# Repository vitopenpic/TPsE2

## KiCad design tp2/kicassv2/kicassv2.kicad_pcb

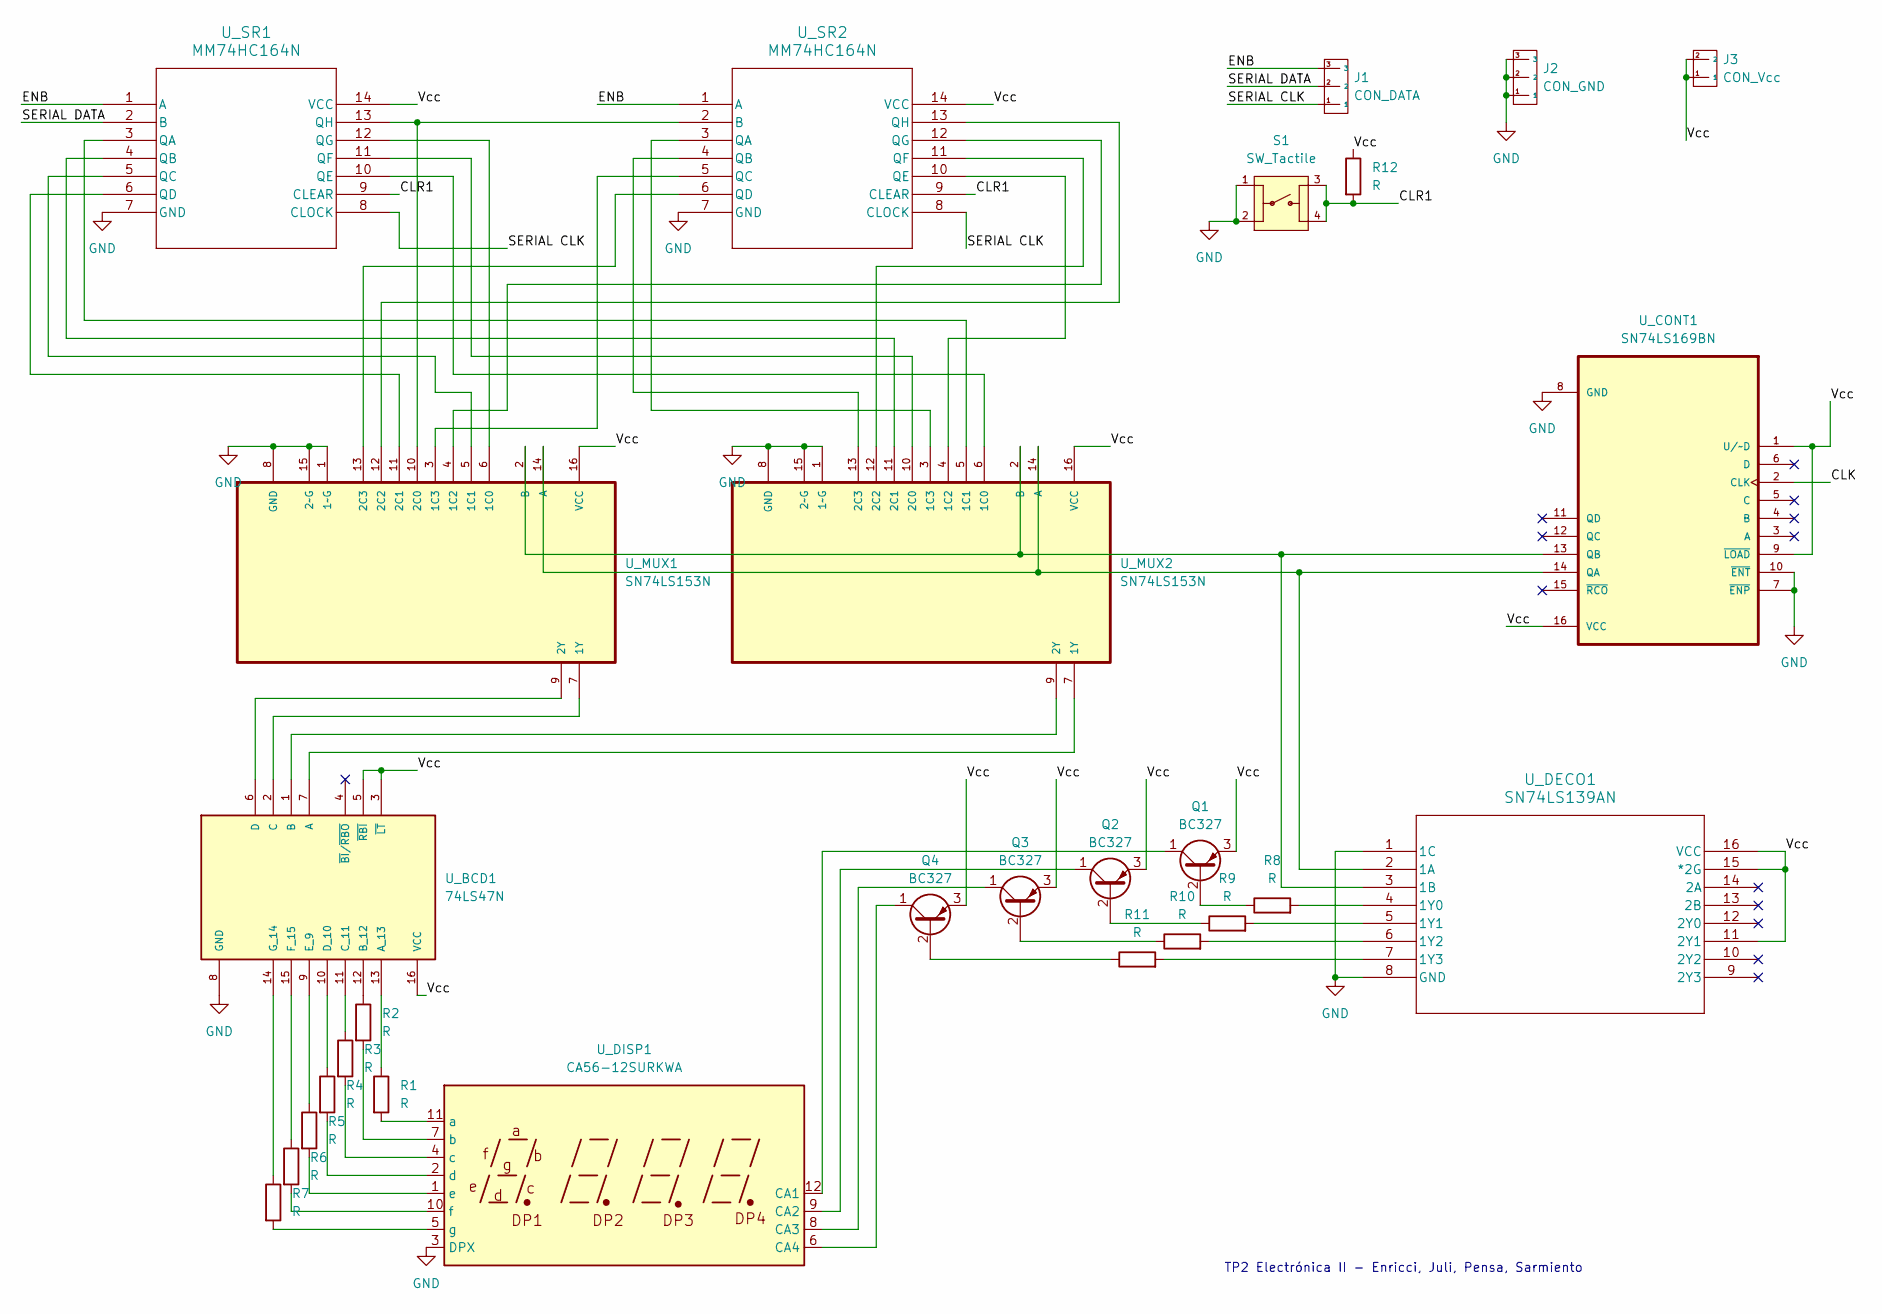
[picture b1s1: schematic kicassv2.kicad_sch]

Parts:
J1: CON_DATA; PinHeader_1x03_P2.54mm_Vertical
J2: CON_GND; PinHeader_1x03_P2.54mm_Vertical
J3: CON_Vcc; PinHeader_1x02_P2.54mm_Vertical
Q1, Q2, Q3, Q4: BC327; TO-92_Inline
R1, R2, R3, R4, R5, R6, R7, R8, R9, R10, R11, R12: R; R_0.25W
S1: SW_Tactile; PARTREV C10
U_BCD1: 74LS47N; PARTREV March 1988
U_CONT1: SN74LS169BN; 74LS169
U_DECO1: SN74LS139AN; 74LS139
U_DISP1: CA56-12SURKWA
U_MUX1, U_MUX2: SN74LS153N; 74LS153; MPN SN74LS153N
U_SR1, U_SR2: MM74HC164N; 74HC164

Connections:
/CLK: U_CONT1.2 (CLK)
/CLR1: R12.2, S1.3, S1.4, U_SR1.9 (CLEAR), U_SR2.9 (CLEAR)
/ENB: J1.3, U_SR1.1 (A), U_SR2.1 (A)
/SERIAL CLK: J1.1, U_SR1.8 (CLOCK), U_SR2.8 (CLOCK)
/SERIAL DATA: J1.2, U_SR1.2 (B)
/Vcc: J3.1, J3.2, Q1.3 (E), Q2.3 (E), Q3.3 (E), Q4.3 (E), R12.1, U_BCD1.3 (~LT), U_BCD1.4 (~BI/~RBO), U_BCD1.5 (~RBI), U_BCD1.16 (VCC), U_CONT1.1 (U/~D), U_CONT1.9 (~LOAD), U_CONT1.16 (VCC), U_DECO1.9 (2Y3), U_DECO1.10 (2Y2), U_DECO1.11 (2Y1), U_DECO1.12 (2Y0), U_DECO1.15 (*2G), U_DECO1.16 (VCC), U_MUX1.16 (VCC), U_MUX2.16 (VCC), U_SR1.14 (VCC), U_SR2.14 (VCC)
GND: J2.1, J2.2, J2.3, S1.1, S1.2, U_BCD1.8 (GND), U_CONT1.7 (~ENP), U_CONT1.8 (GND), U_CONT1.10 (~ENT), U_DECO1.1 (1C), U_DECO1.8 (GND), U_DISP1.3 (DPX), U_MUX1.1 (1~G), U_MUX1.8 (GND), U_MUX1.15 (2~G), U_MUX2.1 (1~G), U_MUX2.8 (GND), U_MUX2.15 (2~G), U_SR1.7 (GND), U_SR2.7 (GND)
unnamed: Q1.2 (B), R8.1
unnamed: Q1.1 (C), U_DISP1.12 (CA1)
unnamed: Q2.2 (B), R9.1
unnamed: Q2.1 (C), U_DISP1.9 (CA2)
unnamed: Q3.2 (B), R10.1
unnamed: Q3.1 (C), U_DISP1.8 (CA3)
unnamed: Q4.2 (B), R11.1
unnamed: Q4.1 (C), U_DISP1.6 (CA4)
unnamed: U_BCD1.7 (A), U_MUX2.7 (1Y)
unnamed: R1.1, U_BCD1.13 (A_13)
unnamed: U_BCD1.1 (B), U_MUX2.9 (2Y)
unnamed: R2.1, U_BCD1.12 (B_12)
unnamed: U_BCD1.2 (C), U_MUX1.7 (1Y)
unnamed: R3.1, U_BCD1.11 (C_11)
unnamed: U_BCD1.6 (D), U_MUX1.9 (2Y)
unnamed: R4.1, U_BCD1.10 (D_10)
unnamed: R5.1, U_BCD1.9 (E_9)
unnamed: R6.1, U_BCD1.15 (F_15)
unnamed: R7.1, U_BCD1.14 (G_14)
unnamed: U_CONT1.14 (QA), U_DECO1.2 (1A), U_MUX1.14 (A), U_MUX2.14 (A)
unnamed: U_CONT1.13 (QB), U_DECO1.3 (1B), U_MUX1.2 (B), U_MUX2.2 (B)
unnamed: R8.2, U_DECO1.4 (1Y0)
unnamed: R9.2, U_DECO1.5 (1Y1)
unnamed: R10.2, U_DECO1.6 (1Y2)
unnamed: R11.2, U_DECO1.7 (1Y3)
unnamed: R1.2, U_DISP1.11 (a)
unnamed: R2.2, U_DISP1.7 (b)
unnamed: R3.2, U_DISP1.4 (c)
unnamed: R4.2, U_DISP1.2 (d)
unnamed: R5.2, U_DISP1.1 (e)
unnamed: R6.2, U_DISP1.10 (f)
unnamed: R7.2, U_DISP1.5 (g)
unnamed: U_MUX1.6 (1C0), U_SR1.12 (QG)
unnamed: U_MUX1.5 (1C1), U_SR1.5 (QC)
unnamed: U_MUX1.4 (1C2), U_SR2.12 (QG)
unnamed: U_MUX1.3 (1C3), U_SR2.5 (QC)
unnamed: U_MUX1.10 (2C0), U_SR1.13 (QH), U_SR2.2 (B)
unnamed: U_MUX1.11 (2C1), U_SR1.6 (QD)
unnamed: U_MUX1.12 (2C2), U_SR2.13 (QH)
unnamed: U_MUX1.13 (2C3), U_SR2.6 (QD)
unnamed: U_MUX2.6 (1C0), U_SR1.10 (QE)
unnamed: U_MUX2.5 (1C1), U_SR1.3 (QA)
unnamed: U_MUX2.4 (1C2), U_SR2.10 (QE)
unnamed: U_MUX2.3 (1C3), U_SR2.3 (QA)
unnamed: U_MUX2.10 (2C0), U_SR1.11 (QF)
unnamed: U_MUX2.11 (2C1), U_SR1.4 (QB)
unnamed: U_MUX2.12 (2C2), U_SR2.11 (QF)
unnamed: U_MUX2.13 (2C3), U_SR2.4 (QB)

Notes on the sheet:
TP2 Electrónica II - Enricci, Juli, Pensa, Sarmiento

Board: 2 copper layers, 28 parts (0 on the bottom side), 54 nets, no tracks yet.

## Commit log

2024-10-26 first commit :{P
2024-11-01 commit pos-entrega
2024-11-07 comienzo electro3
2024-11-14 agregados codigos de verilog del campus
2024-11-17 antirebote y deteccion de tecla
2024-11-21 facu es gay
2024-11-21 cambios en un par de cosas
2024-11-21 modulo de operacion
2024-11-21 nuevos modulos y cambios, hagan algo jeropas
2024-11-22 lola puta
2024-11-22 en teoria ta
2024-11-22 aaaaa iaia
2024-11-23 puse comentarios, leanlos
2024-11-23 actualizaciones
2024-11-23 cambios
2024-11-23 correccion de errores
2024-11-23 actualizaciones corrigiendo errores
2024-11-23 actualizaciones con suma y resta
2024-11-28 Cambios en nombres
2024-11-28 cambios ndeaaaaaa
2024-11-29 listo teclado
2024-11-29 elimine un archivo que estaba al pedo
2024-11-29 cambio de directorios. mas prolijo
2024-11-29 cambio un testbench de lugar
